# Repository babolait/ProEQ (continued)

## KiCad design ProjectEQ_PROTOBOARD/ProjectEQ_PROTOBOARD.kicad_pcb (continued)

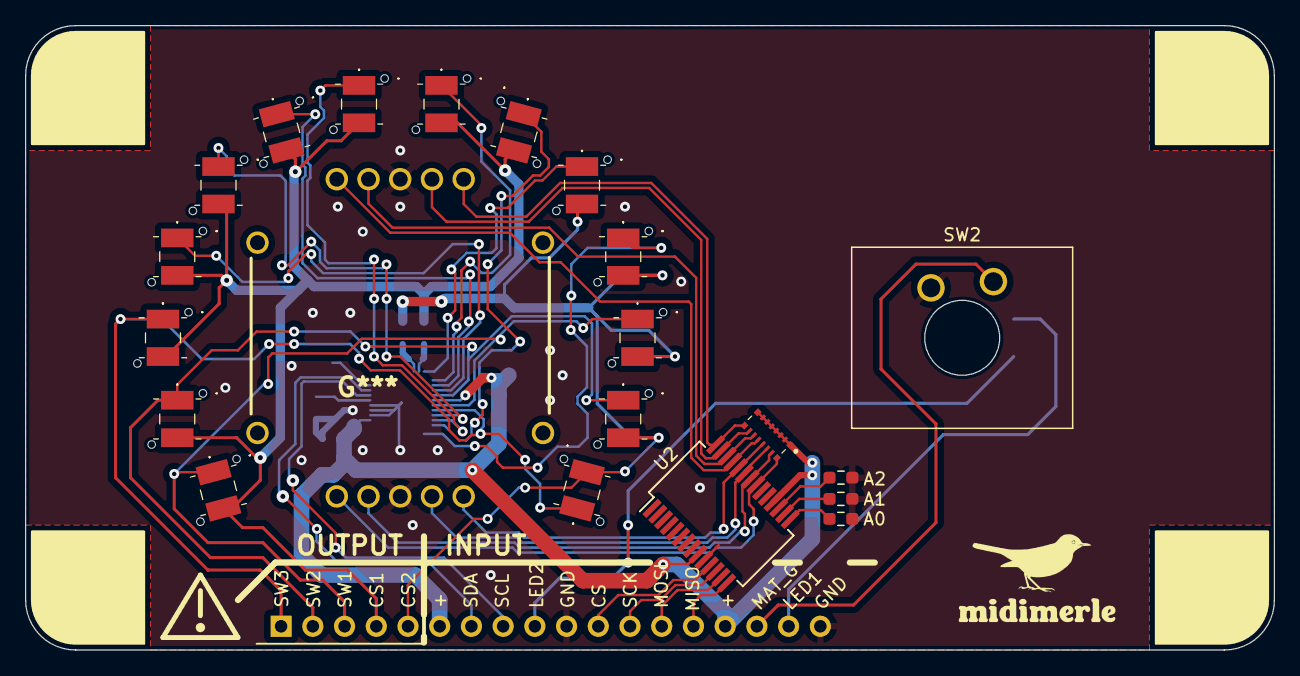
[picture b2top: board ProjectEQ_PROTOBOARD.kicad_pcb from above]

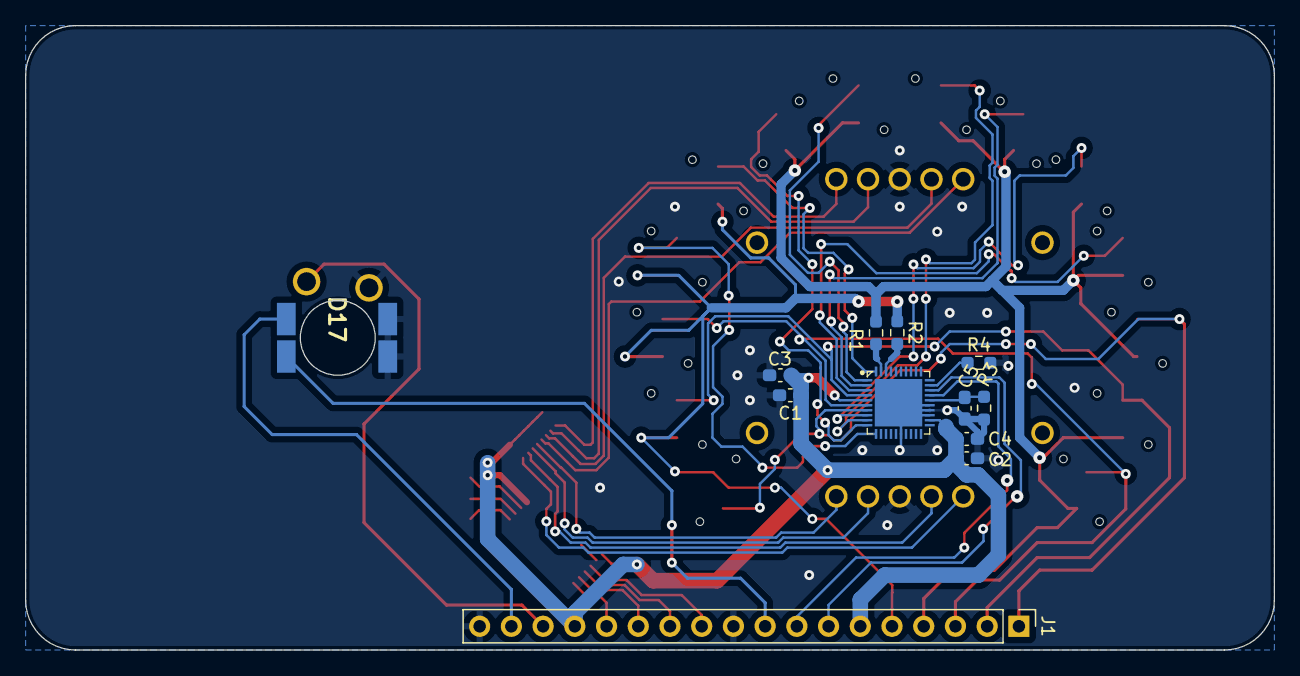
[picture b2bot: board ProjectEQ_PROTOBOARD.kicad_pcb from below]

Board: 2 copper layers, 100.0 x 50.0 mm, 49 parts (13 on the bottom side), 39 nets.

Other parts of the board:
FID1: Fiducial; midimerleKicad symbol
U**: VLP450R
U**#2, U**#3, U**#4, U**#5, U**#6, U**#7, U**#8, U**#9, U**#10, U**#11, U**#12, U**#13, U**#14: VLP450R

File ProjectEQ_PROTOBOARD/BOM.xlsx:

Id | Designator | Footprint | Quantity | Designation | Supplier and ref | Column1 | _1
1 | D8,D3,D5,D14,D11,D10,D13,D12,D1,D4,D7,D2,D6,D9 | SMLZ24E2N3TT86 | 15 | LED_inv | 846-SMLZ24E2N3TT86CT-ND
2 | IC1 | EAW0J-B24-AE0128L | 1 | EAW0J-B24-AE0128L | EAW0J-B24-AE0128L-ND
3 | A0,A2,A1 | R_0603_1608Metric_Pad0.98x0.95mm_HandSolder | 3 | 0 | RMCF0603ZT0R00CT-ND
4 | TP_CS1,TP_D1,TP_D2 | PinHeader_1x01_P2.54mm_Vertical | 0 | TestPoint
5 | U**,U**,U**,U**,U**,U**,U**,U**,U**,U**,U**,U**,U**,U** | VLP450R | 14 | VLP450R | 492-1869-ND
6 | RN1 | EXB2HV472JV | 1 | EXB-2HV472JV | Y1472CT-ND
7 | U2 | SSOP-28_5.3x10.2mm_P0.65mm | 1 | MCP23S17_SO | MCP23S17T-E/SSCT-ND
8 | REF** | carte_Fille | 0 | carte_Fille
9 | SW2 | SW_Matias_QC | 0 | Matias QUIET Click
10 | R2,R1 | R_0603_1608Metric_Pad0.98x0.95mm_HandSolder | 2 | 20 | P20.00BYCT-ND
11 | J2 | PinHeader_1x13_P2.54mm_Vertical | 1 | Conn_01x13
12 | D17 | SMLZ24E2N3TT86_SPEMAT | 0 | LED_inv | 846-SMLZ24E2N3TT86CT-ND
13 | R3 | R_0603_1608Metric_Pad0.98x0.95mm_HandSolder | 1 | 100k | 311-100KHRCT-ND
14 | IC2 | IS31FL3743A | 1 | IS31FL3743A-QULS4-TR | 2521-IS31FL3743A-QULS4-TRCT-ND
15 | C4,C1,C5 | C_0603_1608Metric_Pad1.08x0.95mm_HandSolder | 3 | 0,1uF | 1276-1935-1-ND
16 | C2,C3 | C_0603_1608Metric_Pad1.08x0.95mm_HandSolder | 2 | 1uF | 1276-1102-1-ND
